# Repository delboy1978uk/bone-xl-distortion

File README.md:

# bone xl distortion pedal

I recently got into electronics, and as a musician, I thought a guitar pedal would be a fun project. I followed this awesome tutorial by Brian Wampler of Wampler 
Pedals https://www.wamplerpedals.com/blog/lifestyle-hobby/2024/08/how-to-design-a-basic-distortion-pedal-circuit/. The circuit is slightly different (I use a 
different op-amp), but all credit for the circuit design should go to Brian. This is my first project learning and using KiCad for PCB design.

## bill of materials

| Reference               | Value      | Qty | Notes
|-------------------------|------------|-----|-----
| BT1                     | 9V         | 1   | 9v in -ve core
| C1,C2                   | 47µF       | 2   | electrolytic
| C3,C10,C11              | 22nF       | 3   | 223
| C4,C8                   | 100pF      | 2   | 101
| C5                      | 47nF       | 1   | 473
| C6                      | 50pF       | 1   | 50
| C7                      | 680nF      | 1   | 684
| C9,C12                  | 1µF        | 2   | 105
| D1,D2                   | LED        | 2   | any colour
| J1,J2                   | AudioJack2 | 2   | guitar in/out
| R1,R2,R3,R7,R11,R12,RV2 | 10kΩ       | 7   | blk brn ora
| R4,R8                   | 1MΩ        | 2   | blk brn grn
| R5                      | 4.7kΩ      | 1   | yel pur red
| R6                      | 2.2kΩ      | 1   | red red red
| R9                      | 680kΩ      | 1   | blu gre yel
| R10                     | 1kΩ        | 1   | bro blk red
| R13                     | 220Ω       | 1   | red red bro
| RV1,RV3                 | 100kΩ      | 2   | pots
| U1                      | LM358      | 1   | dual op amp
| U2                      | J201       | 1   | jfet

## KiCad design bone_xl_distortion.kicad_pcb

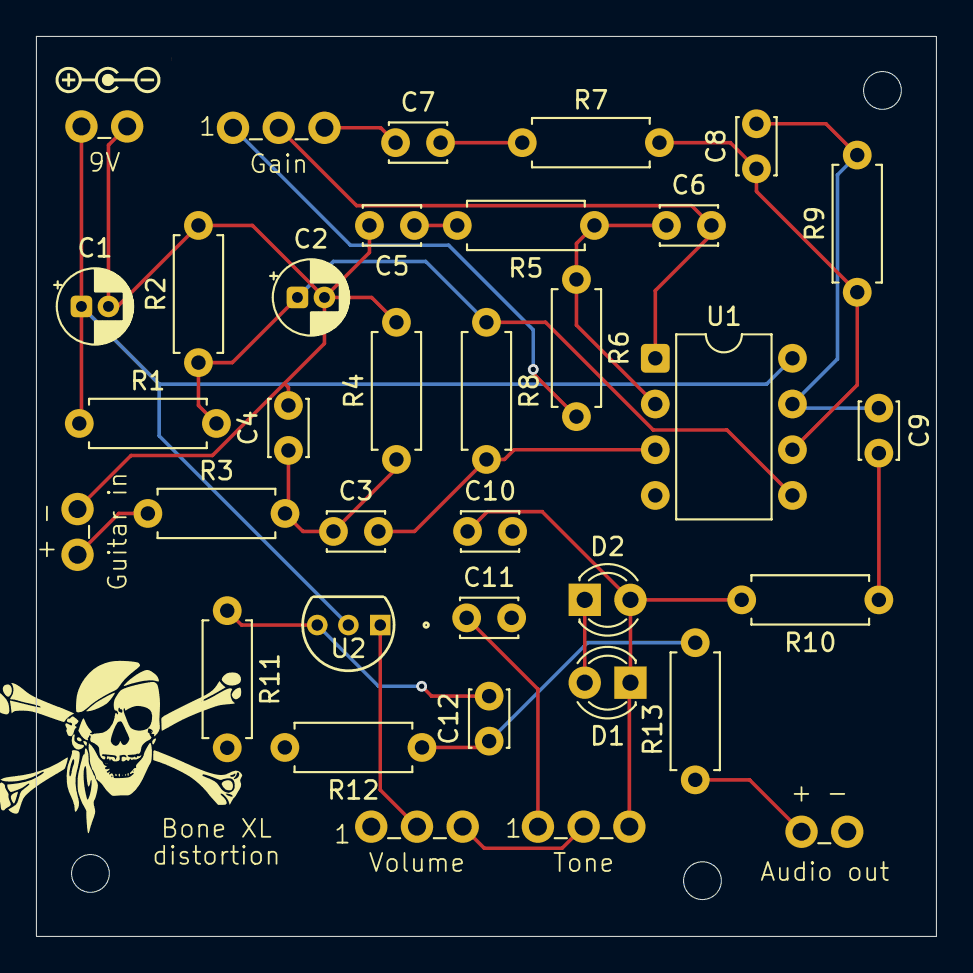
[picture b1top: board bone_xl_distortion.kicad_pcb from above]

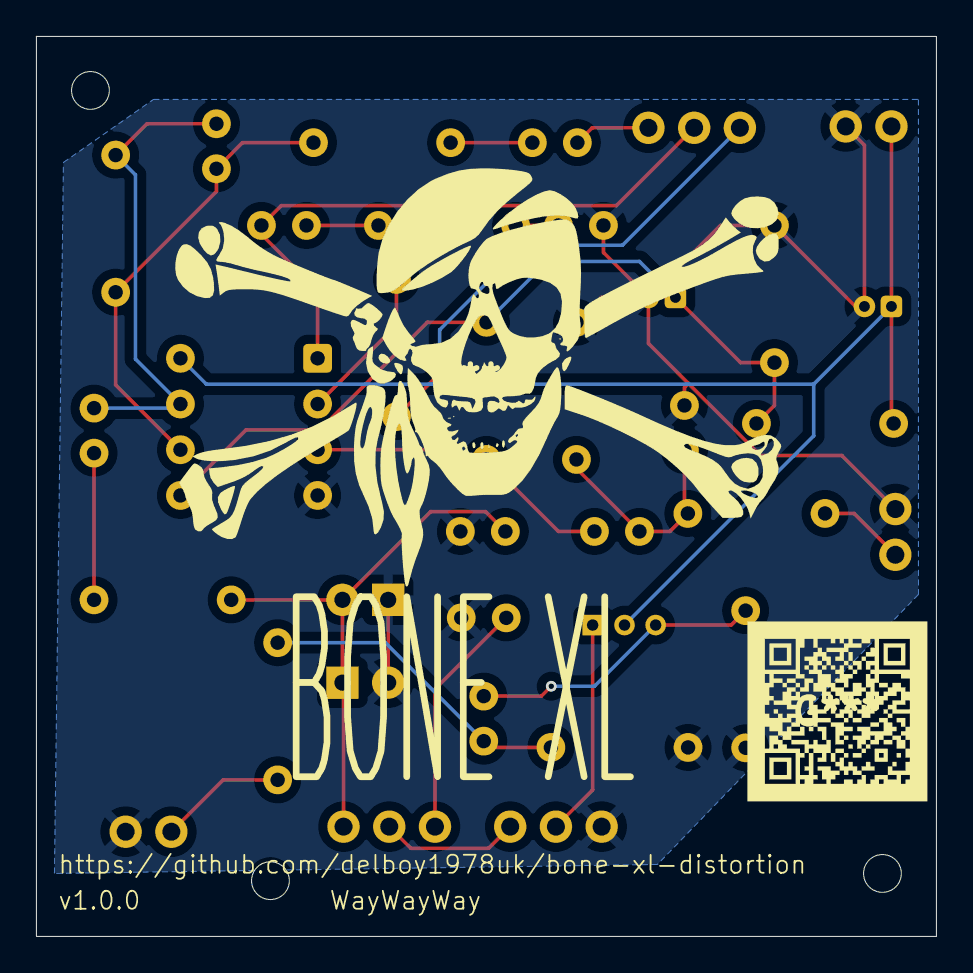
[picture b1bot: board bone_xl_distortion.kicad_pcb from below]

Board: 2 copper layers, 50.0 x 50.0 mm, 47 parts (2 on the bottom side), 22 nets.

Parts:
1, 1#2, 1#3: Text; text
9V: 9V; THT_Wire_Holes_x2
+ -: Text; text
+ -#2: Text; text
Audio out: AudioJack2; THT_Offboard_Audio
BONE XL: Text; text
Bone XL: Text; text
C1, C2: 47µF; CP_Radial_D4.0mm_P1.50mm
C3, C10, C11: 22nF; C_Disc_D3.0mm_W2.0mm_P2.50mm
C4, C8: 100pF; C_Disc_D3.0mm_W2.0mm_P2.50mm
C5: 47nF; C_Disc_D3.0mm_W2.0mm_P2.50mm
C6: 50pF; C_Disc_D3.0mm_W2.0mm_P2.50mm
C7: 680nF; C_Disc_D3.0mm_W2.0mm_P2.50mm
C9, C12: 1µF; C_Disc_D3.0mm_W2.0mm_P2.50mm
D1, D2: LED; LED_D3.0mm
Gain: 100kΩ; THT_Wire_Holes_x3
Guitar in: AudioJack2; THT_Offboard_Audio
R1, R2, R3, R7, R11, R12: 10kΩ; R_Axial_DIN0207_L6.3mm_D2.5mm_P7.62mm_Horizontal
R4, R8: 1MΩ; R_Axial_DIN0207_L6.3mm_D2.5mm_P7.62mm_Horizontal
R5: 4.7kΩ; R_Axial_DIN0207_L6.3mm_D2.5mm_P7.62mm_Horizontal
R6: 2.2kΩ; R_Axial_DIN0207_L6.3mm_D2.5mm_P7.62mm_Horizontal
R9: 680kΩ; R_Axial_DIN0207_L6.3mm_D2.5mm_P7.62mm_Horizontal
R10: 1kΩ; R_Axial_DIN0207_L6.3mm_D2.5mm_P7.62mm_Horizontal
R13: 220Ω; R_Axial_DIN0207_L6.3mm_D2.5mm_P7.62mm_Horizontal
Tone: 10kΩ; THT_Wire_Holes_x3
U1: LM358; DIP-8_W7.62mm
U2: J201; TO-92-3_4P58X4P58_ONS
Volume: 100kΩ; THT_Wire_Holes_x3
WayWayWay: Text; text
distortion: Text; text
https://github.com/delboy1978uk/bone-xl-distortion: Text; text
mount hole: MountingHole_2.1mm
v1.0.0: Text; text

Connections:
/Vref: C2.1, R1.2, R2.1, R8.1, U1.5 (+)
GND: 9V.2 (-), Audio out.T, C1.2, C2.2, C4.2, C5.2, C10.2, C11.2, D1.2 (A), D2.1 (K), Guitar in.T, R2.2, R4.2, R11.2, R12.2, U1.4 (V-), Volume.1
unnamed: C3.1, C4.1, R3.2, R4.1
unnamed: C5.1, R5.2
unnamed: C6.2, Gain.2, U1.1
unnamed: C7.1, Gain.3
unnamed: C7.2, R7.1
unnamed: C8.2, C9.1, R9.2, U1.7
unnamed: C9.2, R10.1
unnamed: C11.1, Tone.1
unnamed: C12.1, R12.1, R13.2
unnamed: C10.1, D1.1 (K), D2.2 (A), R10.2, Tone.3
unnamed: Guitar in.S, R3.1
unnamed: Audio out.S, R13.1
unnamed: Gain.1, R6.2
unnamed: Tone.2, Volume.3
unnamed: C3.2, R8.2, U1.3 (+)
unnamed: C6.1, R5.1, R6.1, U1.2 (-)
unnamed: C8.1, R7.2, R9.1, U1.6 (-)
unnamed: U2.1 (D), Volume.2
unnamed: C12.2, R11.1, U2.3 (G)
VCC: 9V.1 (+), C1.1, R1.1, U1.8 (V+), U2.2 (S)

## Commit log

2025-07-19 Bone XL distortion schematic
2025-07-19 add readme
2025-07-21 updating footprints
2025-07-25 finish pcb design minus silkscreen clipping and manufacturer board settings
2025-07-26 add PCBWay product marker
2025-07-26 add copper zones
2025-07-26 ignore silkscreen violations
2025-07-26 add images for documentation
2025-07-26 add version to silksdcreen
2025-07-26 add gerber files
2025-07-26 add gerbers
2025-08-05 update reADME with images and bill of materials
2025-08-05 update docs
2025-08-07 readme
2025-08-08 add schematic to readme
